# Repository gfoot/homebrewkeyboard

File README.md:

# George's homebrew keyboard

Schematics, board layouts, and code for adding a homebrew keyboard to your electronics projects

This one uses a parallel interface, ideal for connecting directly to the address and data bus of something like a 6502.

I also have one with a serial interface, more tailored for Arduino - let me know if you're interested and I'll publish it as a separate project.

# Schematic

# Bill of materials

* 8x resistor, 10k or thereabouts
* 8x diode, e.g. 1N4007
* 66x 4-pin push-switch with 5.08mmx5.08mm (0.2") pin pitch
* 1x 74LS138 address decoder
* 1x 74LS374 8-bit latch/register with tri-state outputs
* 1x 15-pin header for connecting wires (ideally horizontal, with bent pins)
* Veroboard - 39 tracks of 64 holes, or larger

# General operation

Connect:
* A0..A2 to the CPU's address bus
* D0..7 to the CPU's data bus
* PHI2 to the CPU's phi2 clock signal (the same one you use to time access to RAM, ROM, etc)
* ~OE to a combination of phi2, R/~W, and some address decoding logic

~OE needs to be kept high unless all of the following are true:
* phi2 is high (indicating the bus is active)
* R/~W is low (indicating a write cycle)
* high address pins map to keyboard I/O region

For the last one, my own 6502 computer simply uses an LS138 fed by the top three address lines, and one of the LS138's outputs drives this logic - the same way I generate chip-select signals for other memory-mapped parts of the computer.

Then the CPU can simply read from the mapped addresses.  The lowest address - for example, $a000 - corresponds to one "row" of keys; each bit is 1 if the corresponding key is not pressed, and 0 if it is pressed.  The next address, $a001, corresponds to the next "row", up to the final row at $a007.  The word "row" refers to the schematic, not the physical layout.

As an example, the shift keys correspond to bit 1 of $a000; the ctrl keys correspond to bit 3.  I think bit 0 is Esc, and bit 2 is the space bar.  $a001's bit 0 corresponds to the tilde/backtick key; bit 1 is probably tab or Q; bit 2 is A; and so on.  The exact layout was tweaked to make it easier to build on veroboard, while also ensuring that rollover works well with modifier keys in particular; as usual for this sort of thing, you need to do a lot more translation in software.

See the [kbd module](code/kbd.6502) which contains a full table of characters by row/column.

# Sample code

See [sample code](code/SampleCode.md) and [kbd module](code/kbd.6502).

# Board layout

The board layout shows the physical layout of the components.  The veroboard tracks run horizontally, and - where they are used - they are shown in dark red.  Green traces indicate fairly short links, mostly made with bare wire.  Pink traces indicate longer insulated wire links.  The (X) marks show where you need to break the existing veroboard tracks.

Some connections occur underneath switches, or pass entirely under a switch.  This doesn't always work well in practice, and I ended up routing some wires differently to this diagram.  It depends on the thickness of the wire and the physical shape of your switches.

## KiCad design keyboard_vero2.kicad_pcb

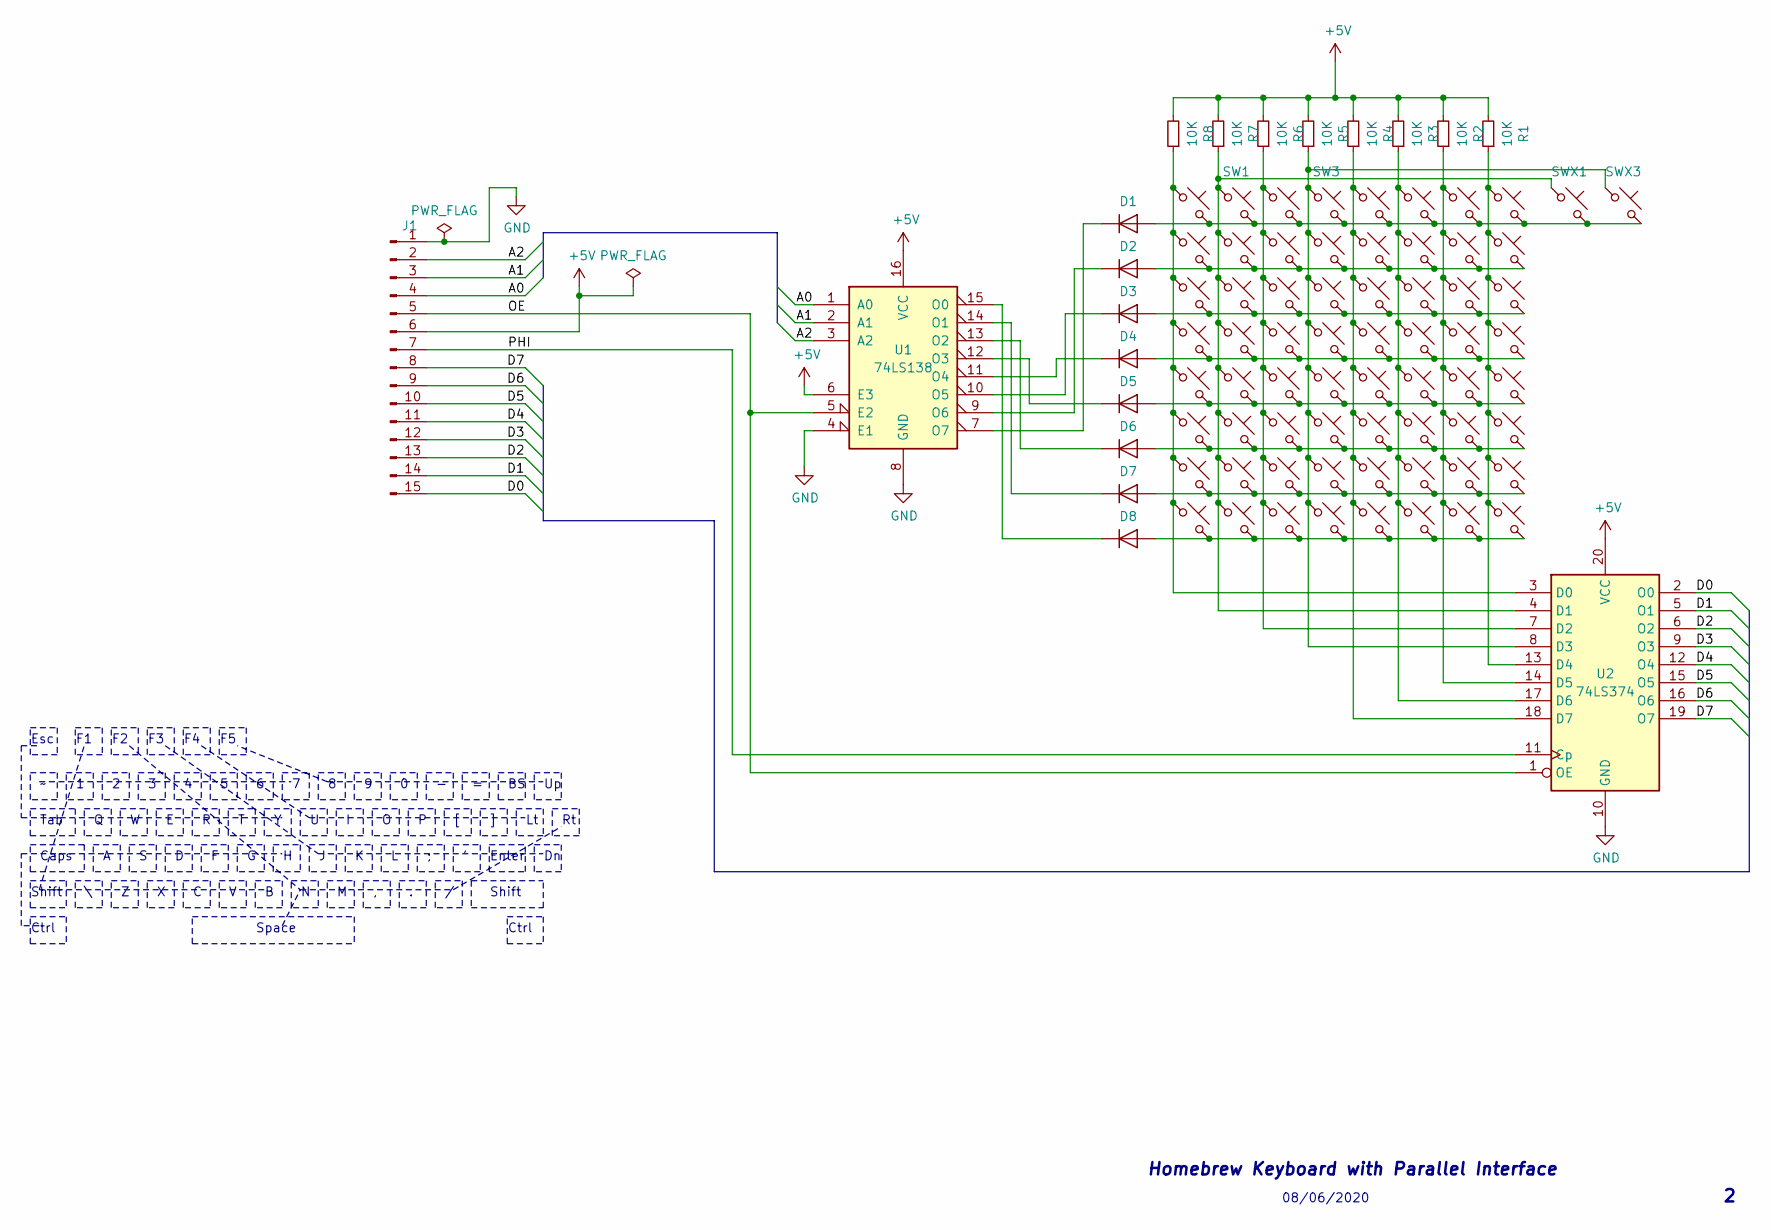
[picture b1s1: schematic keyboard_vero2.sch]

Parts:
D1, D2, D3, D4, D5, D6, D7, D8: 1K; D_DO-35_SOD27_P7.62mm_Horizontal
J1: Conn_01x15_Male; PinHeader_1x15_P2.54mm_Horizontal
R1, R2, R3, R4, R5, R6, R7, R8: 10K; R_Axial_DIN0204_L3.6mm_D1.6mm_P7.62mm_Horizontal
SW0, SW1, SW2, SW3, SW4, SW5, SW6, SW7, SW8, SW9, SW10, SW11, SW12, SW13, SW14, SW15, SW16, SW17, SW18, SW19, SW20, SW21, SW22, SW23, SW24, SW25, SW26, SW27, SW28, SW29, SW30, SW31, SW32, SW33, SW34, SW35, SW36, SW37, SW38, SW39, SW40, SW41, SW42, SW43, SW44, SW45, SW46, SW47, SW48, SW49, SW50, SW51, SW52, SW53, SW54, SW55, SW56, SW57, SW58, SW59, SW60, SW61, SW62, SW63: SW_Push_45deg; SW_PUSH_6mm
SWX1, SWX3: SW_Push_45deg; SW_PUSH_6mm
U1: 74LS138; DIP-16_W7.62mm
U2: 74LS374; DIP-20_W7.62mm

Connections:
+5V: J1.6, R1.2, R2.2, R3.2, R4.2, R5.2, R6.2, R7.2, R8.2, U1.6 (E3), U1.16 (VCC), U2.20 (VCC)
/A0: J1.4, U1.1 (A0)
/A1: J1.3, U1.2 (A1)
/A2: J1.2, U1.3 (A2)
/D0: J1.15, U2.2 (O0)
/D1: J1.14, U2.5 (O1)
/D2: J1.13, U2.6 (O2)
/D3: J1.12, U2.9 (O3)
/D4: J1.11, U2.12 (O4)
/D5: J1.10, U2.15 (O5)
/D6: J1.9, U2.16 (O6)
/D7: J1.8, U2.19 (O7)
/PHI: J1.7, U2.11 (Cp)
unnamed: D1.1 (K), U1.7 (O7)
unnamed: D1.2 (A), SW0.2, SW1.2, SW2.2, SW3.2, SW4.2, SW5.2, SW6.2, SW7.2, SWX1.2, SWX3.2
unnamed: D2.1 (K), U1.9 (O6)
unnamed: D2.2 (A), SW8.2, SW9.2, SW10.2, SW11.2, SW12.2, SW13.2, SW14.2, SW15.2
unnamed: D3.1 (K), U1.10 (O5)
unnamed: D3.2 (A), SW16.2, SW17.2, SW18.2, SW19.2, SW20.2, SW21.2, SW22.2, SW23.2
unnamed: D4.1 (K), U1.11 (O4)
unnamed: D4.2 (A), SW24.2, SW25.2, SW26.2, SW27.2, SW28.2, SW29.2, SW30.2, SW31.2
unnamed: D5.1 (K), U1.12 (O3)
unnamed: D5.2 (A), SW32.2, SW33.2, SW34.2, SW35.2, SW36.2, SW37.2, SW38.2, SW39.2
unnamed: D6.1 (K), U1.13 (O2)
unnamed: D6.2 (A), SW40.2, SW41.2, SW42.2, SW43.2, SW44.2, SW45.2, SW46.2, SW47.2
unnamed: D7.1 (K), U1.14 (O1)
unnamed: D7.2 (A), SW48.2, SW49.2, SW50.2, SW51.2, SW52.2, SW53.2, SW54.2, SW55.2
unnamed: D8.1 (K), U1.15 (O0)
unnamed: D8.2 (A), SW56.2, SW57.2, SW58.2, SW59.2, SW60.2, SW61.2, SW62.2, SW63.2
unnamed: R1.1, SW7.1, SW15.1, SW23.1, SW31.1, SW39.1, SW47.1, SW55.1, SW63.1, U2.13 (D4)
unnamed: R2.1, SW6.1, SW14.1, SW22.1, SW30.1, SW38.1, SW46.1, SW54.1, SW62.1, U2.14 (D5)
unnamed: R3.1, SW5.1, SW13.1, SW21.1, SW29.1, SW37.1, SW45.1, SW53.1, SW61.1, U2.17 (D6)
unnamed: R4.1, SW4.1, SW12.1, SW20.1, SW28.1, SW36.1, SW44.1, SW52.1, SW60.1, U2.18 (D7)
unnamed: R5.1, SW3.1, SW11.1, SW19.1, SW27.1, SW35.1, SW43.1, SW51.1, SW59.1, SWX3.1, U2.8 (D3)
unnamed: R6.1, SW2.1, SW10.1, SW18.1, SW26.1, SW34.1, SW42.1, SW50.1, SW58.1, U2.7 (D2)
unnamed: R7.1, SW1.1, SW9.1, SW17.1, SW25.1, SW33.1, SW41.1, SW49.1, SW57.1, SWX1.1, U2.4 (D1)
unnamed: R8.1, SW0.1, SW8.1, SW16.1, SW24.1, SW32.1, SW40.1, SW48.1, SW56.1, U2.3 (D0)

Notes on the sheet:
Shift
Tab
Caps
Ctrl
Space
Esc
Enter
Homebrew Keyboard with Parallel Interface
08/06/2020

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
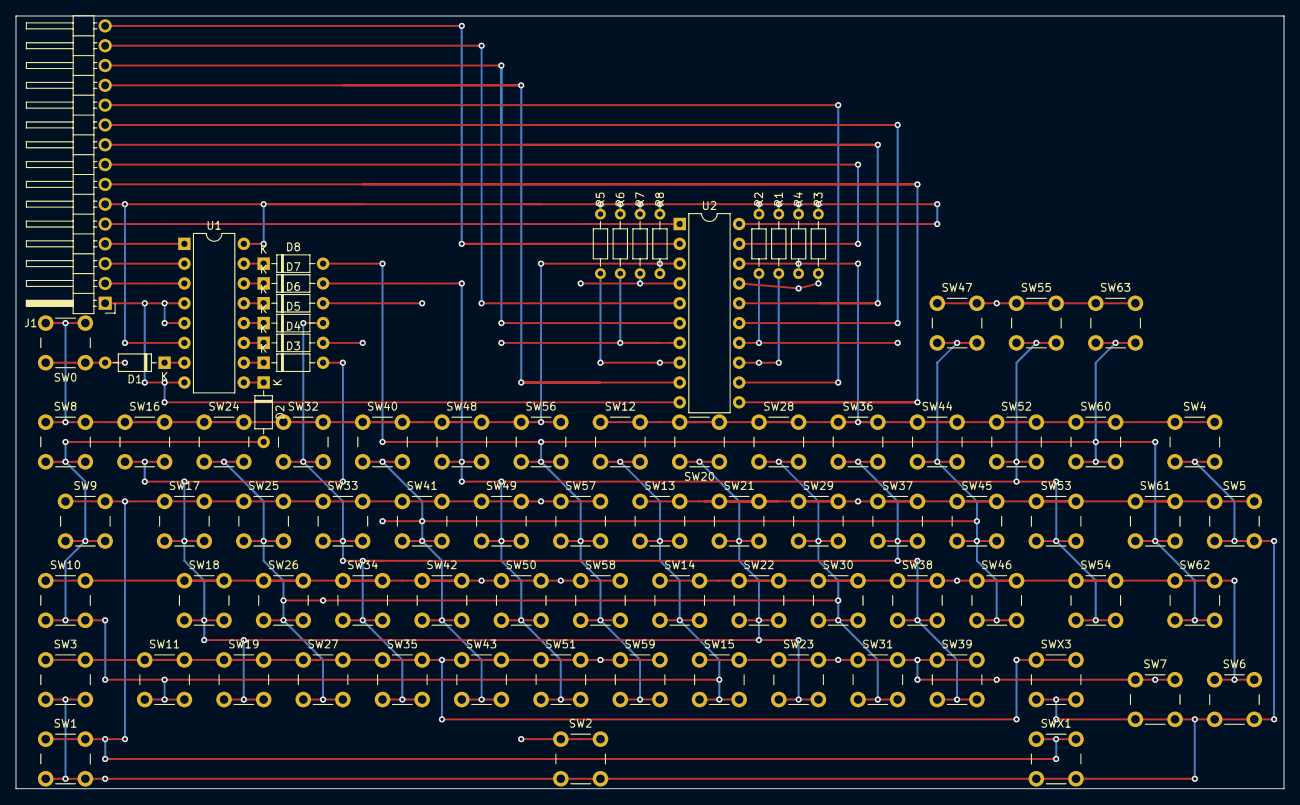
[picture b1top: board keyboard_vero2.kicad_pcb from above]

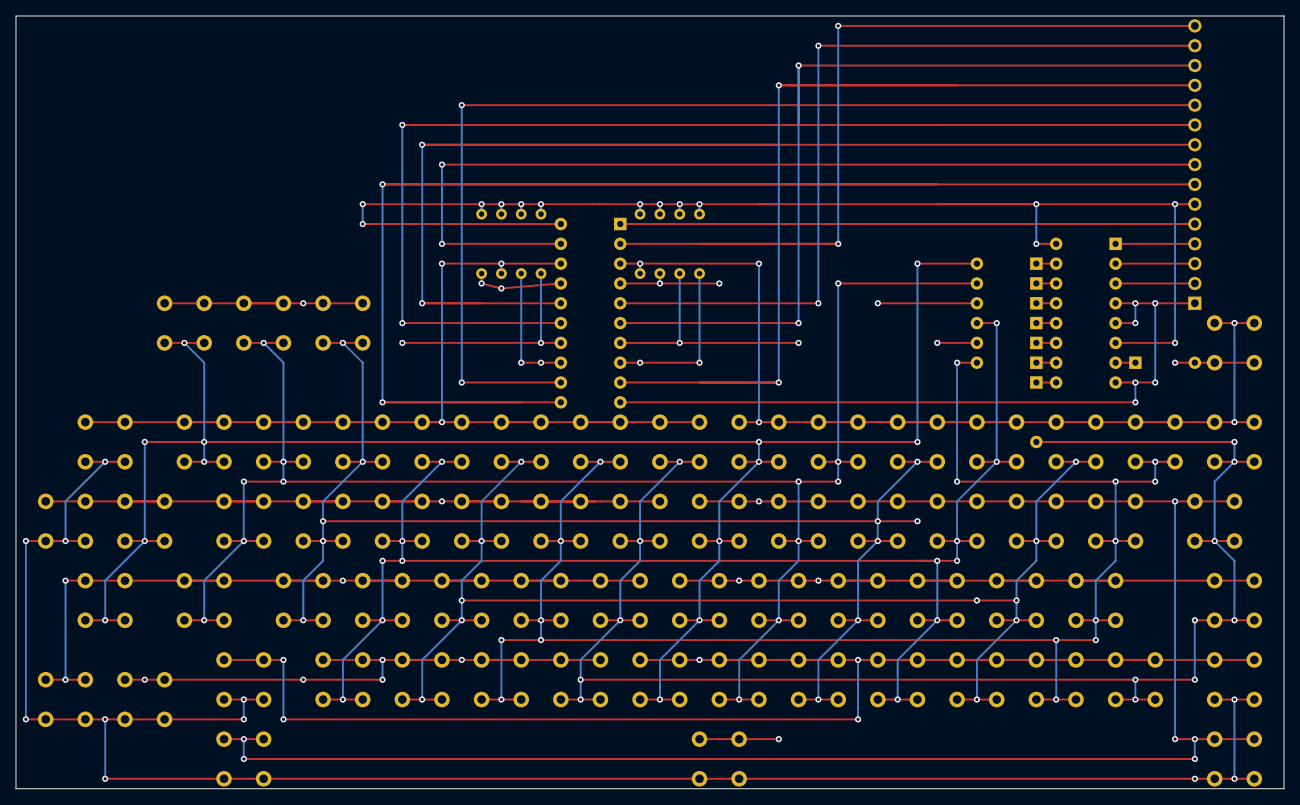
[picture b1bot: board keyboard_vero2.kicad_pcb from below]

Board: 4 copper layers, 162.6 x 99.1 mm, 85 parts (85 on the bottom side), 39 nets.

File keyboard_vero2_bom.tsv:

Reference, Quantity, Value, Footprint, Datasheet
D1 D2 D4 D5 D6 D7 D8 D3 ,8,"1K","Diode_THT:D_DO-35_SOD27_P7.62mm_Horizontal","~"
J1 ,1,"Conn_01x15_Male","Connector_PinHeader_2.54mm:PinHeader_1x15_P2.54mm_Horizontal","~"
R8 R7 R6 R5 R4 R3 R2 R1 ,8,"10K","Resistor_THT:R_Axial_DIN0204_L3.6mm_D1.6mm_P7.62mm_Horizontal","~"
SW0 SW1 SW2 SW3 SW4 SW5 SW6 SW7 SW8 SW9 SW10 SW11 SW12 SW13 SW14 SW15 SW16 SW17 SW18 SW19 SW20 SW21 SW22 SW23 SW24 SW25 SW26 SW27 SW28 SW29 SW30 SW31 SW32 SW33 SW34 SW35 SW36 SW37 SW38 SW39 SW40 SW41 SW42 SW43 SW44 SW45 SW46 SW47 SW48 SW49 SW50 SW51 SW52 SW53 SW54 SW55 SW56 SW57 SW58 SW59 SW60 SW61 SW62 SW63 SWX1 SWX3 ,66,"SW_Push_45deg","keyboard_vero2:SW_PUSH_6mm","~"
U1 ,1,"74LS138","Package_DIP:DIP-16_W7.62mm","http://www.ti.com/lit/gpn/sn74LS138"
U2 ,1,"74LS374","Package_DIP:DIP-20_W7.62mm","http://www.ti.com/lit/gpn/sn74LS374"

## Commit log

2020-06-08 Initial checkin - not quite up-to-date
2020-06-08 Updated schematic to match final build; created BOM
2020-06-08 Add annotated schematic to README.md
2020-06-08 Add photo of assembled boards
2020-06-08 Unlink ~OE from LS138's enable input
2020-06-08 Add board layout image
2020-06-08 Rename to csv in case it works better in github
2020-06-08 Rename it back and convert commas to tabs
2020-06-09 Add sample code and library code; move KiCad stuff into a subdirectory
2020-06-09 Add references to sample code
